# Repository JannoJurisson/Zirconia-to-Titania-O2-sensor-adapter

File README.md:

# Zirconia-to-Titania-O2-sensor-adapter
Adaper to translate a zirconia oxygen sensor voltage output (0-1V) to titania sensor signal (resistance or 0-5V)

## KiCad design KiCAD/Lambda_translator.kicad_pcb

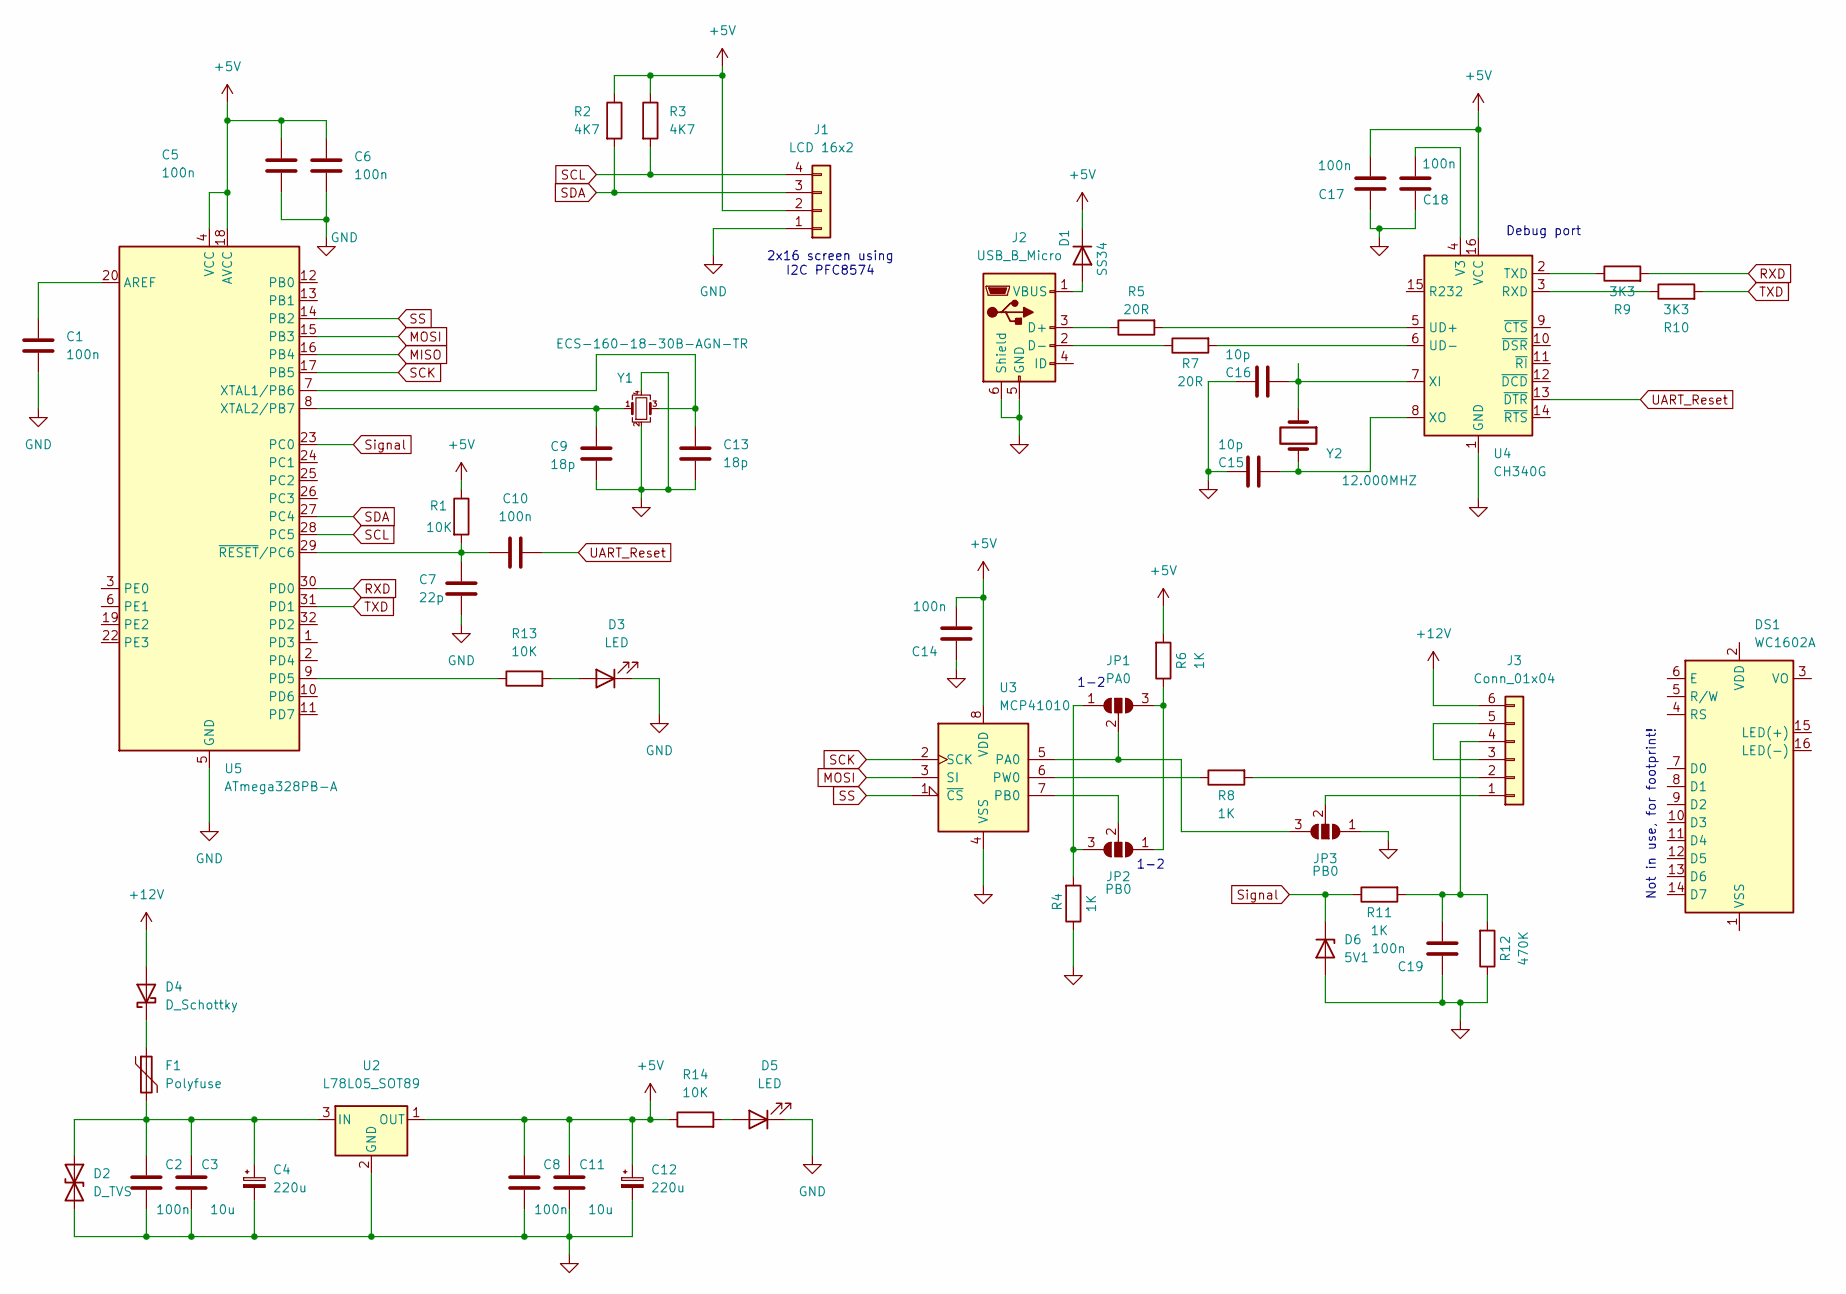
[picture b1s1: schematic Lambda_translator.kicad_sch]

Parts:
C1: 100n; R_0603_1608Metric
C2, C8, C14, C17, C18, C19: 100n; C_0603_1608Metric_Pad1.08x0.95mm_HandSolder
C3, C11: 10u; C_1206_3216Metric_Pad1.33x1.80mm_HandSolder
C4: 220u; CP_Elec_10x10
C5, C6, C10: 100n; C_0603_1608Metric
C7: 22p; C_0603_1608Metric
C9, C13: 18p; C_0805_2012Metric
C12: 220u; CP_Elec_6.3x5.9
C15, C16: 10p; C_0603_1608Metric_Pad1.08x0.95mm_HandSolder
D1: SS34; D_SMA
D2: D_TVS; D_SMA
D3, D5: LED; LED_1206_3216Metric
D4: D_Schottky; D_SMA
D6: 5V1; D_MiniMELF
DS1: WC1602A
F1: Polyfuse; R_2512_6332Metric
J1: LCD 16x2; PinHeader_1x04_P2.54mm_Vertical
J2: USB_B_Micro; USB_Micro-B_Molex_47346-0001
J3: Conn_01x04; PhoenixContact_MC_1,5_6-G-5.08_1x06_P5.08mm_Horizontal
JP1: PA0; SolderJumper-3_P1.3mm_Open_RoundedPad1.0x1.5mm
JP2, JP3: PB0; SolderJumper-3_P1.3mm_Open_RoundedPad1.0x1.5mm
R1, R13, R14: 10K; R_0603_1608Metric
R2, R3: 4K7; R_0603_1608Metric
R4, R6, R8, R11: 1K; R_0603_1608Metric_Pad0.98x0.95mm_HandSolder
R5, R7: 20R; R_0603_1608Metric_Pad0.98x0.95mm_HandSolder
R9, R10: 3K3; R_0603_1608Metric_Pad0.98x0.95mm_HandSolder
R12: 470K; R_0603_1608Metric_Pad0.98x0.95mm_HandSolder
U2: L78L05_SOT89; SOT-89-3
U3: MCP41010; SOIC-8_3.9x4.9mm_P1.27mm
U4: CH340G; SOIC-16_3.9x9.9mm_P1.27mm
U5: ATmega328PB-A; TQFP-32_7x7mm_P0.8mm
Y1: ECS-160-18-30B-AGN-TR; Crystal_SMD_Abracon_ABM3B-4Pin_5.0x3.2mm
Y2: 12.000MHZ; Crystal_SMD_5032-2Pin_5.0x3.2mm

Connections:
+5V: C5.2, C6.2, C8.1, C11.1, C12.1, C14.2, C17.2, D1.1 (K), J1.2, R1.1, R2.1, R3.1, R6.2, R14.1, U2.1 (OUT), U3.8 (VDD), U4.16 (VCC), U5.4 (VCC), U5.18 (AVCC)
+12V: D4.2 (A), J3.6
GND: C1.1, C2.2, C3.2, C4.2, C5.1, C6.1, C7.1, C8.2, C9.2, C11.2, C12.2, C13.2, C14.1, C15.2, C16.2, C17.1, C18.1, C19.1, D2.2 (A2), D3.1 (K), D5.1 (K), D6.2 (A), J1.1, J2.5 (GND), J2.6 (Shield), JP3.1 (A), R4.1, R12.1, U2.2 (GND), U3.4 (VSS), U4.1 (GND), U5.5 (GND), U5.21 (GND), Y1.2, Y1.4
MISO: U5.16 (PB4)
MOSI: U3.3 (SI), U5.15 (PB3)
unnamed: D1.2 (A), J2.1 (VBUS)
unnamed: C2.1, C3.1, C4.1, D2.1 (A1), F1.2, U2.3 (IN)
unnamed: D3.2 (A), R13.2
unnamed: D4.1 (K), F1.1
unnamed: D5.2 (A), R14.2
unnamed: J2.3 (D+), R5.1
unnamed: J2.2 (D-), R7.1
unnamed: J3.1, JP3.2 (C)
unnamed: J3.2, R8.2
unnamed: J3.3, J3.5
unnamed: C19.2, J3.4, R11.2, R12.2
unnamed: JP1.1 (A), JP2.3 (B), R4.2
unnamed: JP1.3 (B), JP2.1 (A), R6.1
unnamed: JP1.2 (C), JP3.3 (B), U3.5 (PA0)
unnamed: JP2.2 (C), U3.7 (PB0)
unnamed: R8.1, U3.6 (PW0)
unnamed: R10.1, U4.3 (RXD)
unnamed: R9.1, U4.2 (TXD)
unnamed: R5.2, U4.5 (UD+)
unnamed: R7.2, U4.6 (UD-)
unnamed: C18.2, U4.4 (V3)
unnamed: C16.1, U4.7 (XI), Y2.1
unnamed: C15.1, U4.8 (XO), Y2.2
unnamed: C1.2, U5.20 (AREF)
unnamed: R13.1, U5.9 (PD5)
unnamed: C13.1, U5.7 (XTAL1/PB6), Y1.3
unnamed: C9.1, U5.8 (XTAL2/PB7), Y1.1
unnamed: C7.2, C10.1, R1.2, U5.29 (~RESET/PC6)
RXD: R9.2, U5.30 (PD0)
SCK: U3.2 (SCK), U5.17 (PB5)
SCL: J1.4, R3.2, U5.28 (PC5)
SDA: J1.3, R2.2, U5.27 (PC4)
SS: U3.1 (~CS), U5.14 (PB2)
Signal: D6.1 (K), R11.1, U5.23 (PC0)
TXD: R10.2, U5.31 (PD1)
UART_Reset: C10.2, U4.13 (~DTR)

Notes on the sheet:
2x16 screen using I2C PFC8574
1-2
Not in use, for footprint!
Debug port

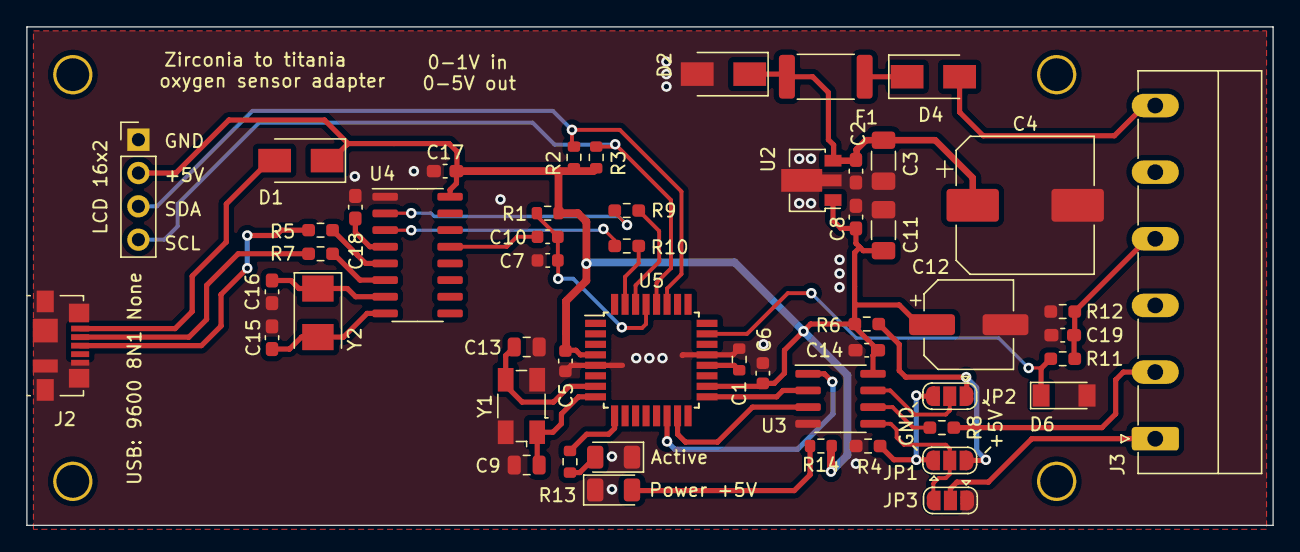
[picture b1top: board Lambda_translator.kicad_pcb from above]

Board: 2 copper layers, 95.0 x 38.0 mm, 53 parts (0 on the bottom side), 40 nets.

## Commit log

2025-10-14 Update ZircToTitania.ino
    Double pot value constrains removed
